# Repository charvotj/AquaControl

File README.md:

# Do not read me :)

It's work in progress and it's still completely uncomplete.

## Pro průběžný progress:
- [Verze odevzdaná jako semestrální](https://github.com/charvotj/AquaControl/tree/main/Semestr%C3%A1lka%20k%20odevzd%C3%A1n%C3%AD)
- [Poslední LaTeX build (text práce)](https://github.com/charvotj/AquaControl/blob/main/latex/CharvotBakalarka2023.pdf)
- [Schéma řídící jednotky (export do pdf)](https://github.com/charvotj/AquaControl/blob/main/latex/obrazky/exportovane/main-board-schematic.pdf)

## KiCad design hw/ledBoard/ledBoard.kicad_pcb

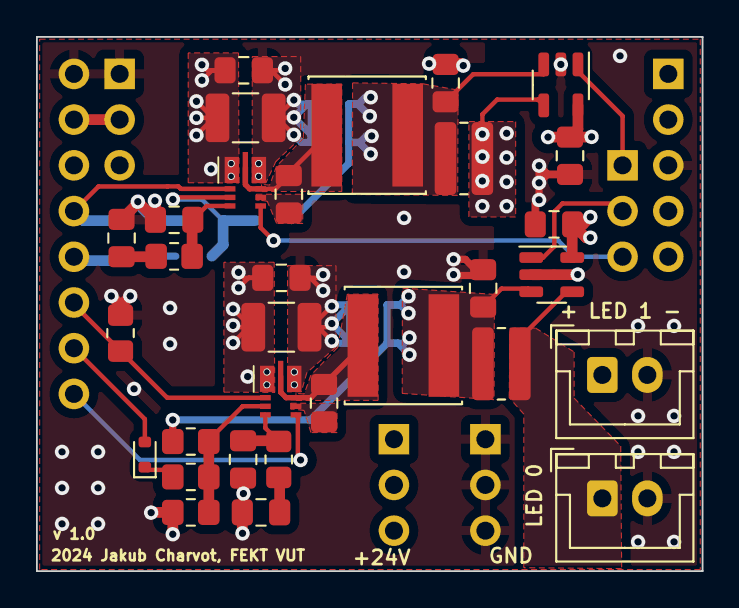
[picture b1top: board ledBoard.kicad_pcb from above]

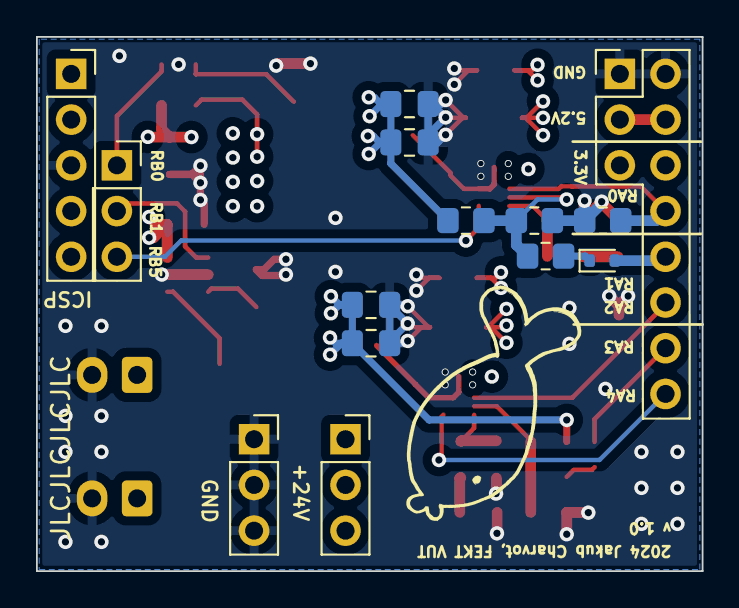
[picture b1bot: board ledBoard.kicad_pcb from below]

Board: 4 copper layers, 37.0 x 29.7 mm, 45 parts (13 on the bottom side), 28 nets.

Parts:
C2, C3: 10uF; C_1210_3225Metric_Pad1.33x2.70mm_HandSolder
C4, C5: 10nF; C_0805_2012Metric_Pad1.18x1.45mm_HandSolder
C6, C14: 6.8nF; C_0805_2012Metric_Pad1.18x1.45mm_HandSolder
C7, C13, C19, C20, C23, C24: 100nF; C_0805_2012Metric_Pad1.18x1.45mm_HandSolder
C8, C9, C10, C15, C16, C17: 22uF; C_0805_2012Metric_Pad1.18x1.45mm_HandSolder
D2, D4: RB501SM; D_SOD-523
J1: Conn_02x11_Socket; LedBoardPinHeader
J2, J3: Conn_01x02; JST_XH_B2B-XH-A_1x02_P2.50mm_Vertical
J5, J6, J9: Conn_01x03_Socket; PinSocket_1x03_P2.54mm_Vertical
J8: Conn_01x05_Socket; PinSocket_1x05_P2.54mm_Vertical
L1, L2: 10uH; L_Changjiang_FNR6045S
R1, R9: 140k; R_0805_2012Metric_Pad1.20x1.40mm_HandSolder
R2, R10: 10k; R_0805_2012Metric_Pad1.20x1.40mm_HandSolder
R3, R7: 47k; R_0805_2012Metric_Pad1.20x1.40mm_HandSolder
R4, R5, R8, R11: 100k; R_0805_2012Metric_Pad1.20x1.40mm_HandSolder
R6, R12: 10m; R_0815_2038Metric_Pad1.20x4.05mm_HandSolder
U1, U2: INA180A4; SOT-23-5
U3, U4: AP63356Q; V-DFN3020-13

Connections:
/5.2V: J1.3, J1.4
/24V: C2.1, C3.1, C4.1, C5.1, J9.1, J9.2, J9.3, U3.1 (VIN), U4.1 (VIN)
/LED_OUT_0: J2.1, R6.1, U1.4 (-)
/LED_OUT_1: J3.1, R12.1, U2.4 (-)
/RA0: J1.8, R8.1, U4.2 (EN)
/RA1: D4.2 (A), J1.10
/RA2: J1.12, R5.1, U3.2 (EN)
/RA3: D2.2 (A), J1.14
/RA4: J1.16, U3.5 (PG)
/RB0: J5.1, U2.1
/RB1: J5.2, U1.1
/RB5: J5.3, U4.5 (PG)
/VDD: C19.1, C20.1, J1.5, J1.6, J8.2, U1.5 (V+), U2.5 (V+)
GND: C2.2, C3.2, C4.2, C5.2, C6.1, C7.1, C8.2, C9.2, C10.2, C13.1, C14.1, C15.2, C16.2, C17.2, C19.2, C20.2, J1.1, J1.2, J2.2, J3.2, J6.1, J6.2, J6.3, J8.3, R2.2, R5.2, R8.2, R10.2, U1.2 (GND), U2.2 (GND), U3.8 (GND), U4.8 (GND)
unnamed: C6.2, R3.2
unnamed: C14.2, R7.2
unnamed: D2.1 (K), R4.2
unnamed: D4.1 (K), R11.2
unnamed: C8.1, C9.1, C10.1, L1.1, R1.1, R6.2, U1.3 (+)
unnamed: C15.1, C16.1, C17.1, L2.1, R9.1, R12.2, U2.3 (+)
unnamed: C24.1, U3.6 (BST)
unnamed: C7.2, R3.1, U3.4 (COMP)
unnamed: R1.2, R2.1, R4.1, U3.3 (FB)
unnamed: C24.2, L1.2, U3.9 (SW)
unnamed: C23.1, U4.6 (BST)
unnamed: C13.2, R7.1, U4.4 (COMP)
unnamed: R9.2, R10.1, R11.1, U4.3 (FB)
unnamed: C23.2, L2.2, U4.9 (SW)

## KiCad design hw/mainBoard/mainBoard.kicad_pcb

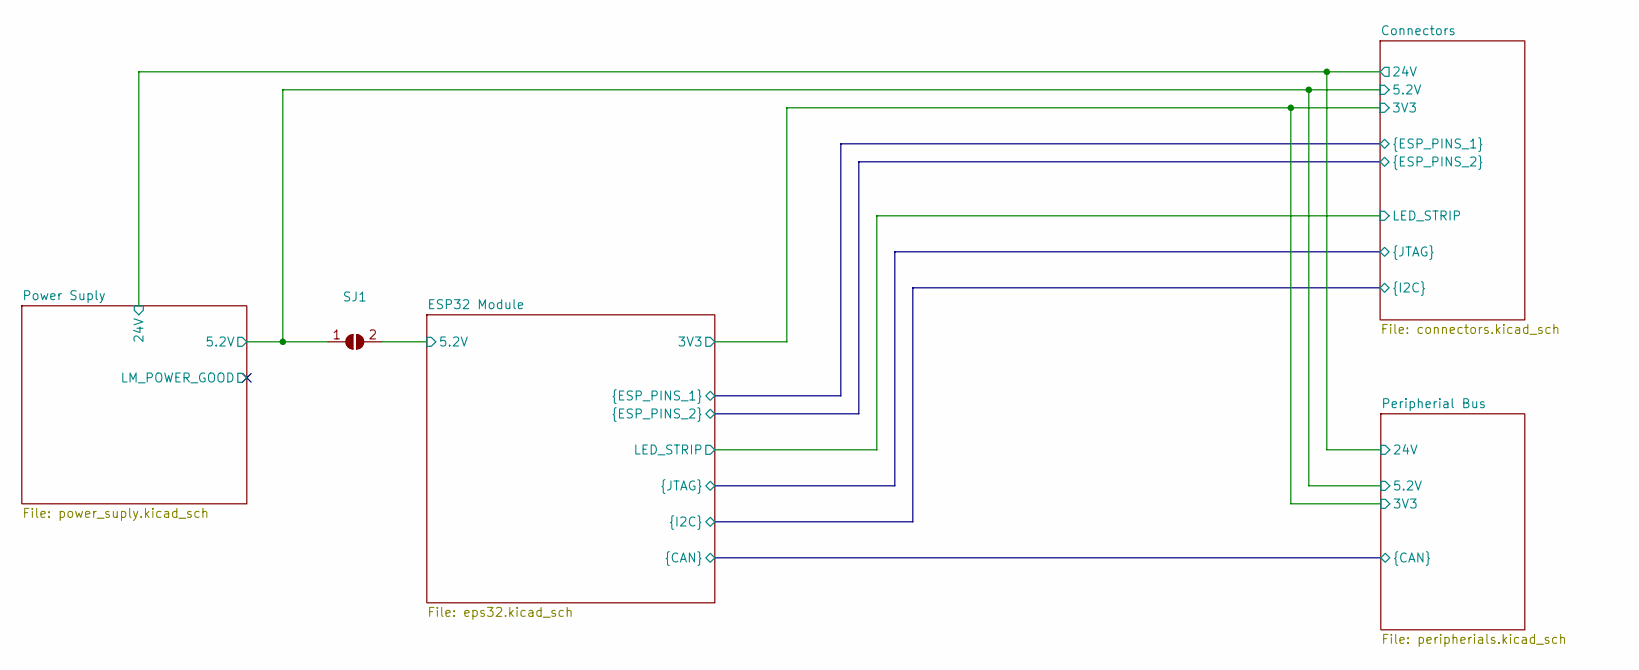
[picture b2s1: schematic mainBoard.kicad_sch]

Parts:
SJ1: SolderJumper_2_Open; SolderJumper-2_P1.3mm_Open_RoundedPad1.0x1.5mm

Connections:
/Connectors/5.2V: SJ1.1 (A), SJ1.2 (B); also elsewhere on the board

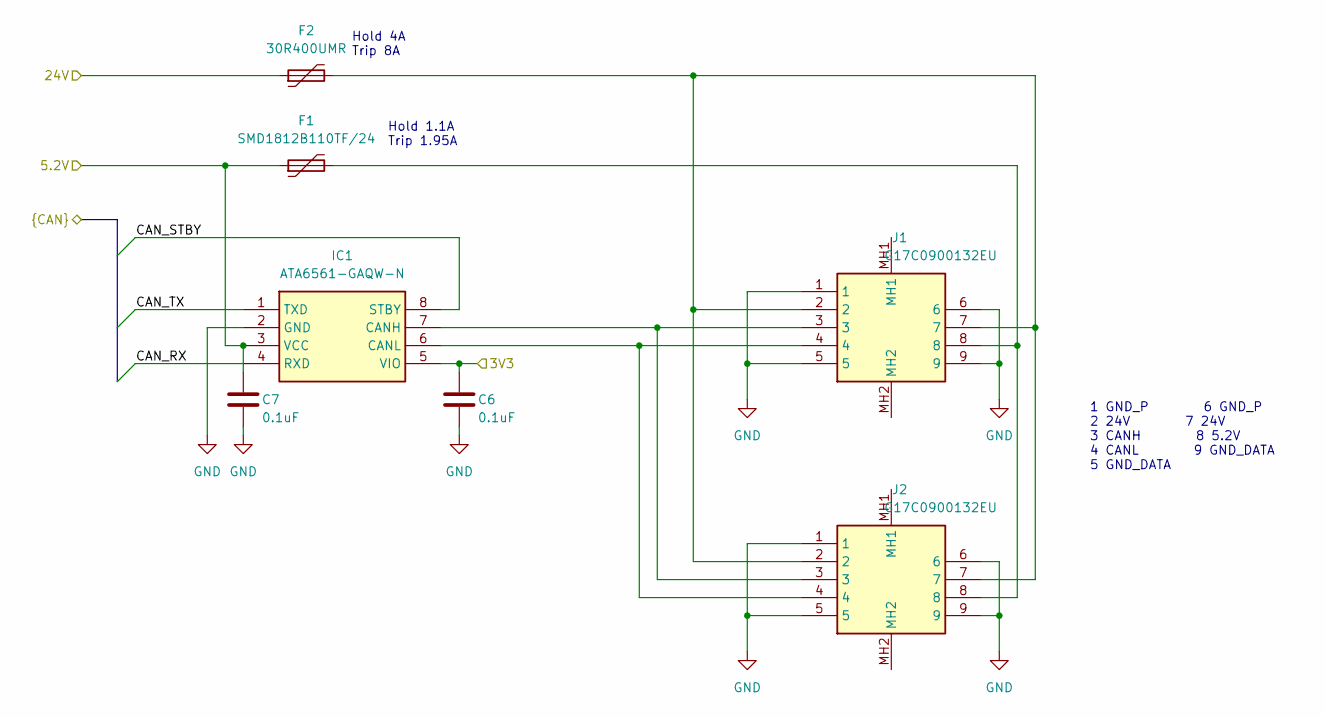
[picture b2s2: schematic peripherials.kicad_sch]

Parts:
C6, C7: 0.1uF; C_1206_3216Metric_Pad1.33x1.80mm_HandSolder
F1: SMD1812B110TF/24; Fuse_1812_4532Metric
F2: 30R400UMR
IC1: ATA6561-GAQW-N; SOIC127P600X175-8N; Mouser Part Number 579-ATA6561-GAQW-N
J1, J2: G17C0900132EU; Mouser Part Number 523-G17C0900132EU

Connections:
/Connectors/5.2V: C7.1, F1.1, IC1.3 (VCC); also elsewhere on the board
/Connectors/24V: F2.1; also elsewhere on the board
/Connectors/CAN_RX: IC1.4 (RXD); also elsewhere on the board
/Connectors/CAN_STBY: IC1.8 (STBY); also elsewhere on the board
/Connectors/CAN_TX: IC1.1 (TXD); also elsewhere on the board
/ESP32 Module/3V3: C6.1, IC1.5 (VIO); also elsewhere on the board
GND: C6.2, C7.2, IC1.2 (GND), J1.1, J1.5, J1.6, J1.9, J2.1, J2.5, J2.6, J2.9; also elsewhere on the board
unnamed: F2.2, J1.2, J1.7, J2.2, J2.7
unnamed: F1.2, J1.8, J2.8
unnamed: IC1.7 (CANH), J1.3, J2.3
unnamed: IC1.6 (CANL), J1.4, J2.4

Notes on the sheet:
Hold 4A Trip 8A
1 GND_P 6 GND_P 2 24V 7 24V 3 CANH 8 5.2V 4 CANL 9 GND_DATA 5 GND_DATA
Hold 1.1A Trip 1.95A

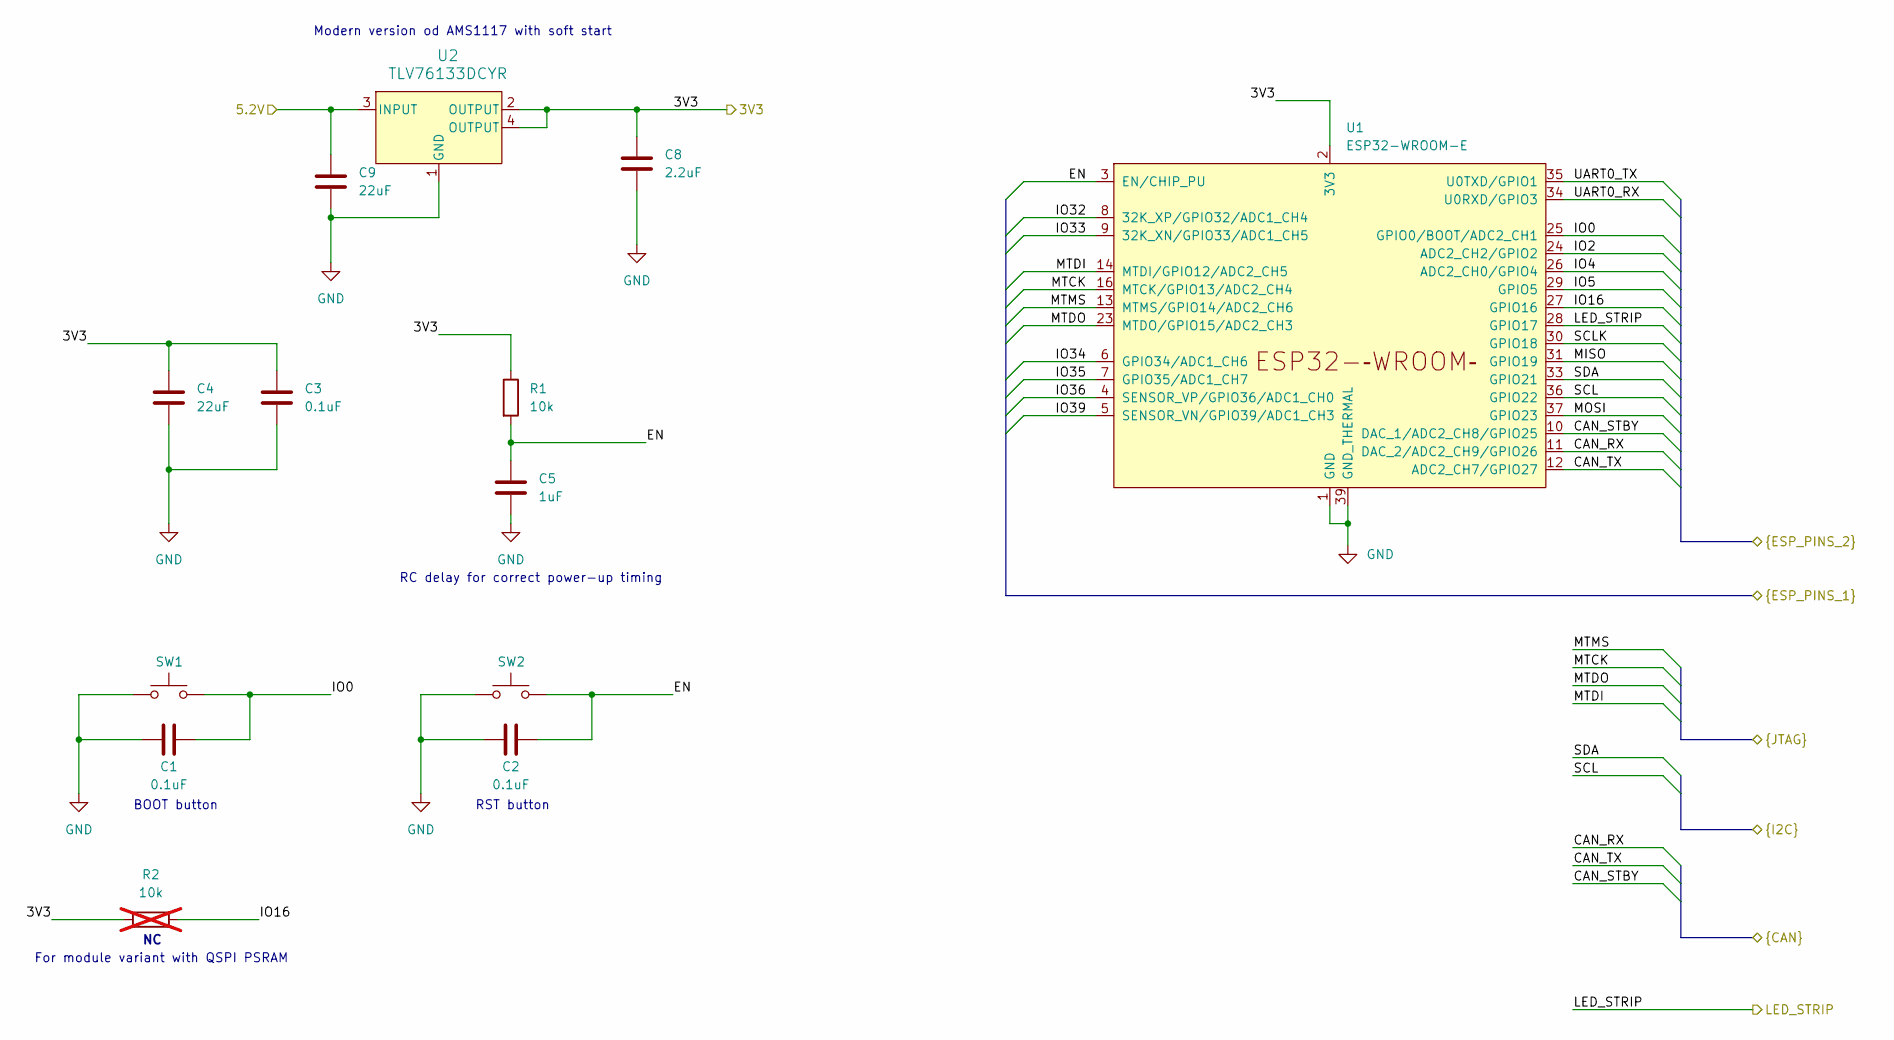
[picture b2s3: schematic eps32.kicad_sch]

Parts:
C1, C2, C3: 0.1uF; C_1206_3216Metric_Pad1.33x1.80mm_HandSolder
C4, C9: 22uF; C_1206_3216Metric_Pad1.33x1.80mm_HandSolder
C5: 1uF; C_1206_3216Metric_Pad1.33x1.80mm_HandSolder
C8: 2.2uF; C_1206_3216Metric_Pad1.33x1.80mm_HandSolder
R1: 10k; R_0805_2012Metric_Pad1.20x1.40mm_HandSolder
R2: 10k; R_0805_2012Metric_Pad1.20x1.40mm_HandSolder; not fitted
SW1, SW2: SW_Push; SW_SPST_B3U-1000P
U1: ESP32-WROOM-E; ESP32-WROOM-32E
U2: TLV76133DCYR; SOT_8DCYR_TEX

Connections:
/Connectors/5.2V: C9.1, U2.3 (INPUT); also elsewhere on the board
/Connectors/CAN_RX: U1.11 (DAC_2/ADC2_CH9/GPIO26); also elsewhere on the board
/Connectors/CAN_STBY: U1.10 (DAC_1/ADC2_CH8/GPIO25); also elsewhere on the board
/Connectors/CAN_TX: U1.12 (ADC2_CH7/GPIO27); also elsewhere on the board
/Connectors/EN: C2.2, C5.1, R1.2, SW2.2, U1.3 (EN/CHIP_PU); also elsewhere on the board
/Connectors/IO0: C1.2, SW1.2, U1.25 (GPIO0/BOOT/ADC2_CH1); also elsewhere on the board
/Connectors/IO2: U1.24 (ADC2_CH2/GPIO2); also elsewhere on the board
/Connectors/IO4: U1.26 (ADC2_CH0/GPIO4); also elsewhere on the board
/Connectors/IO5: U1.29 (GPIO5); also elsewhere on the board
/Connectors/IO16: R2.2, U1.27 (GPIO16); also elsewhere on the board
/Connectors/IO32: U1.8 (32K_XP/GPIO32/ADC1_CH4); also elsewhere on the board
/Connectors/IO33: U1.9 (32K_XN/GPIO33/ADC1_CH5); also elsewhere on the board
/Connectors/IO34: U1.6 (GPIO34/ADC1_CH6); also elsewhere on the board
/Connectors/IO35: U1.7 (GPIO35/ADC1_CH7); also elsewhere on the board
/Connectors/IO36: U1.4 (SENSOR_VP/GPIO36/ADC1_CH0); also elsewhere on the board
/Connectors/IO39: U1.5 (SENSOR_VN/GPIO39/ADC1_CH3); also elsewhere on the board
/Connectors/LED_STRIP: U1.28 (GPIO17); also elsewhere on the board
/Connectors/MISO: U1.31 (GPIO19); also elsewhere on the board
/Connectors/MOSI: U1.37 (GPIO23); also elsewhere on the board
/Connectors/MTCK: U1.16 (MTCK/GPIO13/ADC2_CH4); also elsewhere on the board
/Connectors/MTDI: U1.14 (MTDI/GPIO12/ADC2_CH5); also elsewhere on the board
/Connectors/MTDO: U1.23 (MTDO/GPIO15/ADC2_CH3); also elsewhere on the board
/Connectors/MTMS: U1.13 (MTMS/GPIO14/ADC2_CH6); also elsewhere on the board
/Connectors/SCL: U1.36 (GPIO22); also elsewhere on the board
/Connectors/SCLK: U1.30 (GPIO18); also elsewhere on the board
/Connectors/SDA: U1.33 (GPIO21); also elsewhere on the board
/Connectors/UART0_RX: U1.34 (U0RXD/GPIO3); also elsewhere on the board
/Connectors/UART0_TX: U1.35 (U0TXD/GPIO1); also elsewhere on the board
/ESP32 Module/3V3: C3.1, C4.1, C8.1, R1.1, R2.1, U1.2 (3V3), U2.2 (OUTPUT), U2.4 (OUTPUT); also elsewhere on the board
GND: C1.1, C2.1, C3.2, C4.2, C5.2, C8.2, C9.2, SW1.1, SW2.1, U1.1 (GND), U1.15 (GND), U1.38 (GND), U1.39 (GND_THERMAL), U2.1 (GND); also elsewhere on the board

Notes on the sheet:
RST button
BOOT button
Modern version od AMS1117 with soft start
For module variant with QSPI PSRAM
RC delay for correct power-up timing

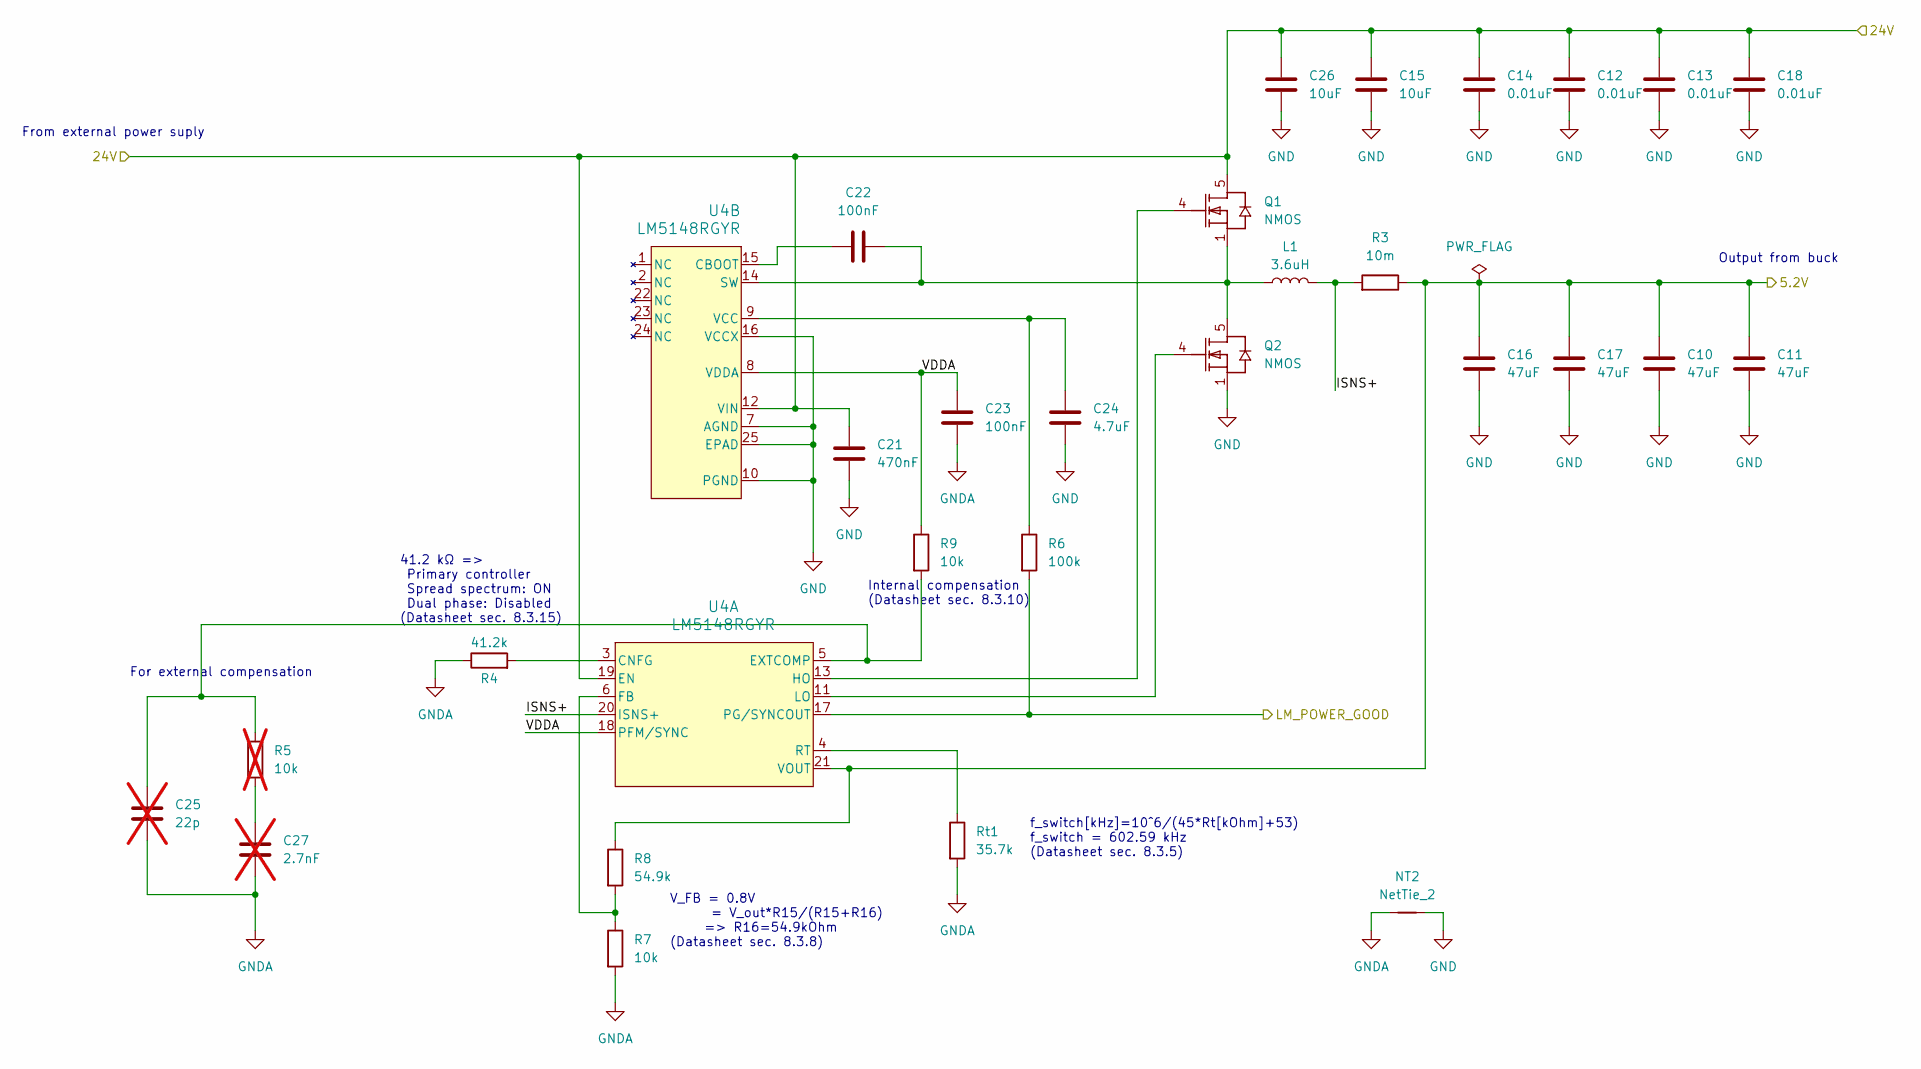
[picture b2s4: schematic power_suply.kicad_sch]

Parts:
C10, C11, C16, C17: 47uF; C_1210_3225Metric_Pad1.33x2.70mm_HandSolder
C12, C13, C14, C18: 0.01uF; C_0805_2012Metric_Pad1.18x1.45mm_HandSolder
C15, C26: 10uF; C_1210_3225Metric_Pad1.33x2.70mm_HandSolder
C21: 470nF; C_0805_2012Metric_Pad1.18x1.45mm_HandSolder
C22, C23: 100nF; C_0805_2012Metric_Pad1.18x1.45mm_HandSolder
C24: 4.7uF; C_0805_2012Metric_Pad1.18x1.45mm_HandSolder
C25: 22p; C_0805_2012Metric_Pad1.18x1.45mm_HandSolder; not fitted
C27: 2.7nF; C_0805_2012Metric_Pad1.18x1.45mm_HandSolder; not fitted
L1: 3.6uH; L_Bourns-SRN8040_8x8.15mm
NT2: NetTie_2; NetTie-2_SMD_Pad0.5mm
Q1, Q2: NMOS; DQJ0008A
R3: 10m; R_0815_2038Metric_Pad1.20x4.05mm_HandSolder
R4: 41.2k; R_0805_2012Metric_Pad1.20x1.40mm_HandSolder
R5: 10k; R_0805_2012Metric_Pad1.20x1.40mm_HandSolder; not fitted
R6: 100k; R_0805_2012Metric_Pad1.20x1.40mm_HandSolder
R7, R9: 10k; R_0805_2012Metric_Pad1.20x1.40mm_HandSolder
R8: 54.9k; R_0805_2012Metric_Pad1.20x1.40mm_HandSolder
Rt1: 35.7k; R_0805_2012Metric_Pad1.20x1.40mm_HandSolder
U4: LM5148RGYR; VQFN24_RGY_TEX

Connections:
/Connectors/5.2V: C10.1, C11.1, C16.1, C17.1, R3.1, R8.1, U4.21 (VOUT); also elsewhere on the board
/Connectors/24V: C12.1, C13.1, C14.1, C15.1, C18.1, C21.1, C26.1, Q1.5, Q1.6 (D), Q1.7 (D), Q1.8 (D), Q1.9, U4.12 (VIN), U4.19 (EN); also elsewhere on the board
/Power Suply/ISNS+: L1.1, R3.2, U4.20 (ISNS+)
/Power Suply/LM_POWER_GOOD: R6.2, U4.17 (PG/SYNCOUT)
/Power Suply/VDDA: C23.1, R9.1, U4.8 (VDDA), U4.18 (PFM/SYNC)
GND: C10.2, C11.2, C12.2, C13.2, C14.2, C15.2, C16.2, C17.2, C18.2, C21.2, C24.2, C26.2, NT2.2, Q2.1, Q2.2 (S), Q2.3 (S), U4.1 (NC), U4.7 (AGND), U4.10 (PGND), U4.16 (VCCX), U4.22 (NC), U4.23 (NC), U4.24 (NC), U4.25 (EPAD); also elsewhere on the board
GNDA: C23.2, C25.2, C27.2, NT2.1, R4.1, R7.2, Rt1.2; also elsewhere on the board
unnamed: C27.1, R5.2
unnamed: C25.1, R5.1, R9.2, U4.5 (EXTCOMP)
unnamed: R7.1, R8.2, U4.6 (FB)
unnamed: Q1.4, U4.13 (HO)
unnamed: Q2.4, U4.11 (LO)
unnamed: Rt1.1, U4.4 (RT)
unnamed: C22.1, U4.15 (CBOOT)
unnamed: C22.2, L1.2, Q1.1, Q1.2 (S), Q1.3 (S), Q2.5, Q2.6 (D), Q2.7 (D), Q2.8 (D), Q2.9, U4.14 (SW)
unnamed: C24.1, R6.1, U4.9 (VCC)

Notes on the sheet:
From external power suply
For external compensation
f_switch[kHz]=10^6/(45*Rt[kOhm]+53) f_switch = 602.59 kHz (Datasheet sec. 8.3.5)
Output from buck
41.2 kΩ => Primary controller Spread spectrum: ON Dual phase: Disabled (Datasheet sec. 8.3.15)
Internal compensation (Datasheet sec. 8.3.10)
V_FB = 0.8V = V_out*R15/(R15+R16) => R16=54.9kOhm (Datasheet sec. 8.3.8)

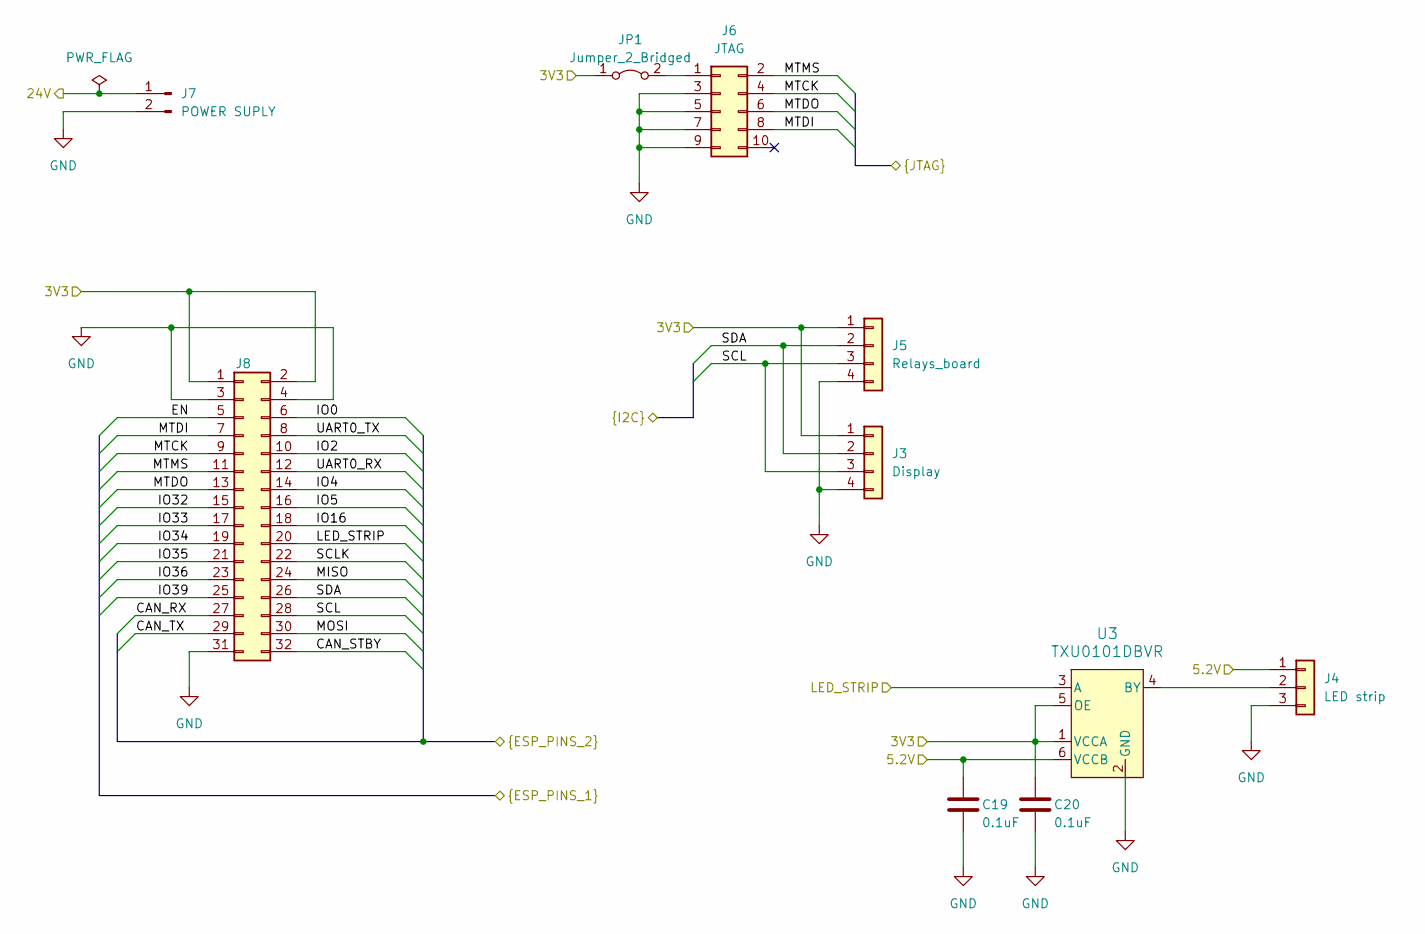
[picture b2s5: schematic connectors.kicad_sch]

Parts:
C19, C20: 0.1uF; C_1206_3216Metric_Pad1.33x1.80mm_HandSolder
J3: Display; JST_XH_B4B-XH-AM_1x04_P2.50mm_Vertical
J4: LED strip; JST_EH_B3B-EH-A_1x03_P2.50mm_Vertical
J5: Relays_board; JST_XH_B4B-XH-AM_1x04_P2.50mm_Vertical
J6: JTAG; PinHeader_2x05_P1.27mm_Vertical
J7: POWER SUPLY; TerminalBlock_Altech_AK300-2_P5.00mm
J8: Conn_02x16_Odd_Even; PinHeader_2x16_P2.54mm_Vertical
JP1: Jumper_2_Bridged; TestPoint_2Pads_Pitch2.54mm_Drill0.8mm
U3: TXU0101DBVR; SOT-23-6-DBV_TEX

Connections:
/Connectors/5.2V: C19.1, J4.1, U3.6 (VCCB); also elsewhere on the board
/Connectors/24V: J7.1; also elsewhere on the board
/Connectors/CAN_RX: J8.27; also elsewhere on the board
/Connectors/CAN_STBY: J8.32; also elsewhere on the board
/Connectors/CAN_TX: J8.29; also elsewhere on the board
/Connectors/EN: J8.5; also elsewhere on the board
/Connectors/IO0: J8.6; also elsewhere on the board
/Connectors/IO2: J8.10; also elsewhere on the board
/Connectors/IO4: J8.14; also elsewhere on the board
/Connectors/IO5: J8.16; also elsewhere on the board
/Connectors/IO16: J8.18; also elsewhere on the board
/Connectors/IO32: J8.15; also elsewhere on the board
/Connectors/IO33: J8.17; also elsewhere on the board
/Connectors/IO34: J8.19; also elsewhere on the board
/Connectors/IO35: J8.21; also elsewhere on the board
/Connectors/IO36: J8.23; also elsewhere on the board
/Connectors/IO39: J8.25; also elsewhere on the board
/Connectors/LED_STRIP: J8.20, U3.3 (A); also elsewhere on the board
/Connectors/MISO: J8.24; also elsewhere on the board
/Connectors/MOSI: J8.30; also elsewhere on the board
/Connectors/MTCK: J6.4, J8.9; also elsewhere on the board
/Connectors/MTDI: J6.8, J8.7; also elsewhere on the board
/Connectors/MTDO: J6.6, J8.13; also elsewhere on the board
/Connectors/MTMS: J6.2, J8.11; also elsewhere on the board
/Connectors/SCL: J3.3, J5.3, J8.28; also elsewhere on the board
/Connectors/SCLK: J8.22; also elsewhere on the board
/Connectors/SDA: J3.2, J5.2, J8.26; also elsewhere on the board
/Connectors/UART0_RX: J8.12; also elsewhere on the board
/Connectors/UART0_TX: J8.8; also elsewhere on the board
/ESP32 Module/3V3: C20.1, J3.1, J5.1, J8.1, J8.2, JP1.1 (A), U3.1 (VCCA), U3.5 (OE); also elsewhere on the board
GND: C19.2, C20.2, J3.4, J4.3, J5.4, J6.3, J6.5, J6.7, J6.9, J7.2, J8.3, J8.4, J8.31, U3.2 (GND); also elsewhere on the board
unnamed: J4.2, U3.4 (BY)
unnamed: J6.1, JP1.2 (B)

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
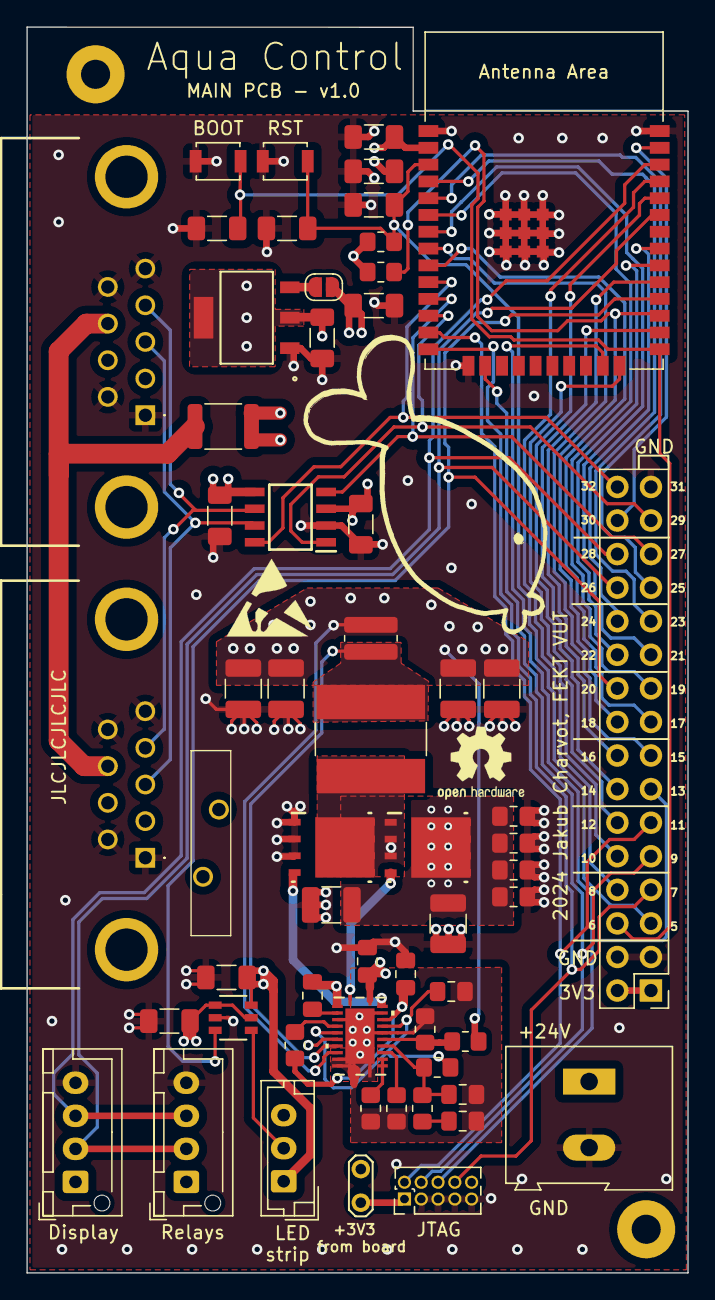
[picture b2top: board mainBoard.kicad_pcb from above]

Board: 4 copper layers, 50.0 x 94.2 mm, 62 parts (0 on the bottom side), 51 nets.

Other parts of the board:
BOOT: SW_Push; SW_SPST_B3U-1000P
NT1: NetTie_2; NetTie-2_SMD_Pad0.5mm
RST: SW_Push; SW_SPST_B3U-1000P
RYBA: LOGO

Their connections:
/Connectors/EN: RST.2; also elsewhere on the board
/Connectors/IO0: BOOT.2; also elsewhere on the board
GND: BOOT.1, NT1.2, RST.1; also elsewhere on the board
GNDA: NT1.1; also elsewhere on the board

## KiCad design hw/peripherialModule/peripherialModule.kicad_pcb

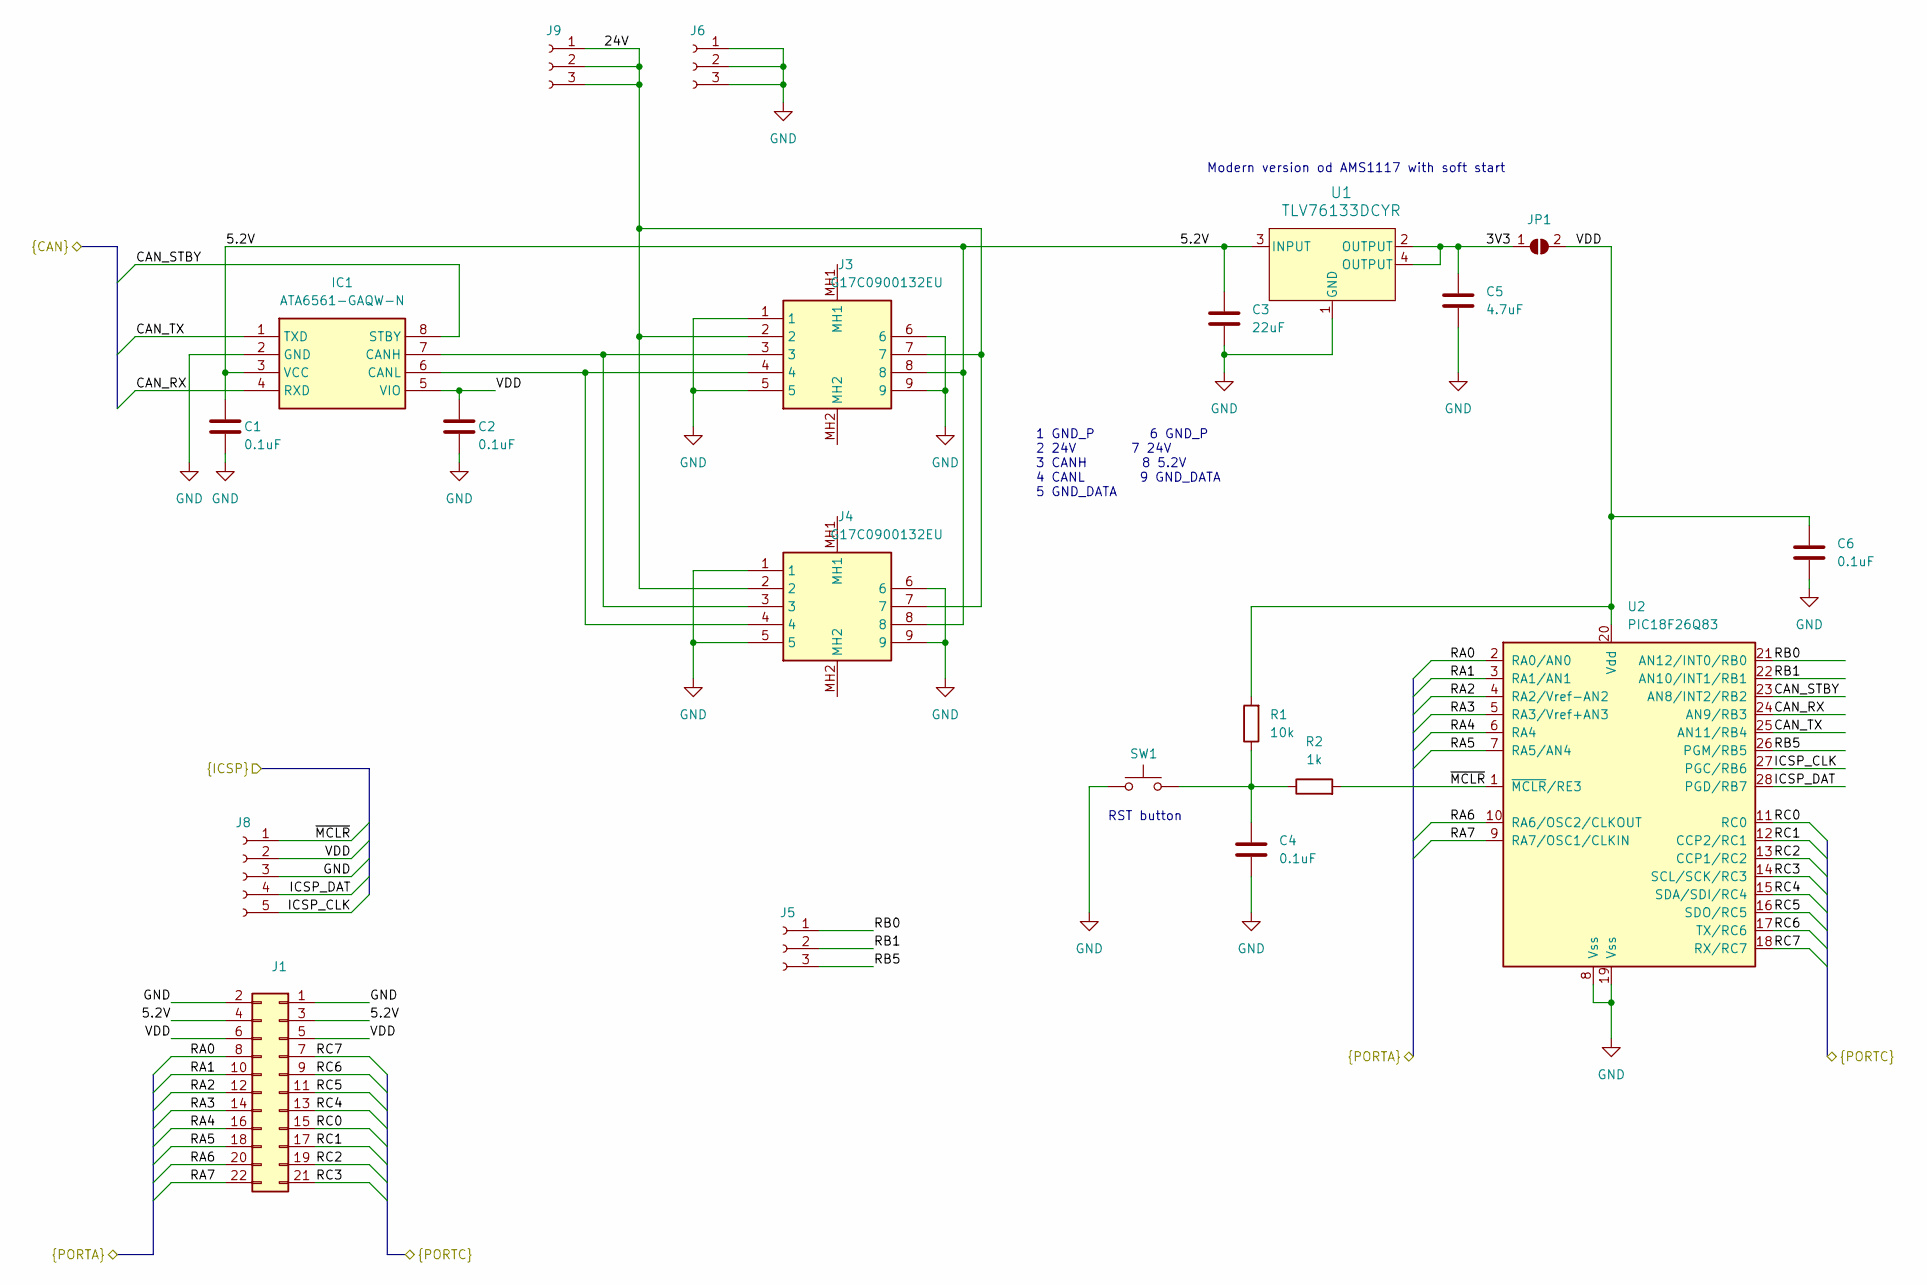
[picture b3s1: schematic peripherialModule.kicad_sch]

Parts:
C1, C2: 0.1uF; C_1206_3216Metric_Pad1.33x1.80mm_HandSolder
C3: 22uF; C_1206_3216Metric_Pad1.33x1.80mm_HandSolder
C4, C6: 0.1uF; C_1206_3216Metric_Pad1.33x1.80mm_HandSolder; Mouser no. 80-C1206C104K5R7210
C5: 4.7uF; C_0805_2012Metric_Pad1.18x1.45mm_HandSolder
IC1: ATA6561-GAQW-N; SOIC127P600X175-8N; Mouser Part Number 579-ATA6561-GAQW-N
J1: Conn_02x11_Socket; PinSocket_2x11_P2.54mm_Vertical
J3, J4: G17C0900132EU; Mouser Part Number 523-G17C0900132EU
J5, J6, J9: Conn_01x03_Socket; PinSocket_1x03_P2.54mm_Vertical
J8: Conn_01x05_Socket; PinSocket_1x05_P2.54mm_Vertical
JP1: SolderJumper_2_Open; SolderJumper-2_P1.3mm_Open_RoundedPad1.0x1.5mm
R1: 10k; R_0805_2012Metric_Pad1.20x1.40mm_HandSolder; Mouser no. 791-RMC20K103FTP
R2: 1k; R_0805_2012Metric_Pad1.20x1.40mm_HandSolder
SW1: SW_Push; SW_SPST_B3U-1000P
U1: TLV76133DCYR; SOT_8DCYR_TEX
U2: PIC18F26Q83; SSOP-28_5.3x10.2mm_P0.65mm

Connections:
/3V3: C5.1, JP1.1 (A), U1.2 (OUTPUT), U1.4 (OUTPUT)
/5.2V: C1.1, C3.1, IC1.3 (VCC), J1.3, J1.4, J3.8, J4.8, U1.3 (INPUT)
/24V: J3.2, J3.7, J4.2, J4.7, J9.1, J9.2, J9.3
/CAN_RX: IC1.4 (RXD), U2.24 (AN9/RB3)
/CAN_STBY: IC1.8 (STBY), U2.23 (AN8/INT2/RB2)
/CAN_TX: IC1.1 (TXD), U2.25 (AN11/RB4)
/ICSP_CLK: J8.5, U2.27 (PGC/RB6)
/ICSP_DAT: J8.4, U2.28 (PGD/RB7)
/RA0: J1.8, U2.2 (RA0/AN0)
/RA1: J1.10, U2.3 (RA1/AN1)
/RA2: J1.12, U2.4 (RA2/Vref-AN2)
/RA3: J1.14, U2.5 (RA3/Vref+AN3)
/RA4: J1.16, U2.6 (RA4)
/RA5: J1.18, U2.7 (RA5/AN4)
/RA6: J1.20, U2.10 (RA6/OSC2/CLKOUT)
/RA7: J1.22, U2.9 (RA7/OSC1/CLKIN)
/RB0: J5.1, U2.21 (AN12/INT0/RB0)
/RB1: J5.2, U2.22 (AN10/INT1/RB1)
/RB5: J5.3, U2.26 (PGM/RB5)
/RC0: J1.15, U2.11 (RC0)
/RC1: J1.17, U2.12 (CCP2/RC1)
/RC2: J1.19, U2.13 (CCP1/RC2)
/RC3: J1.21, U2.14 (SCL/SCK/RC3)
/RC4: J1.13, U2.15 (SDA/SDI/RC4)
/RC5: J1.11, U2.16 (SDO/RC5)
/RC6: J1.9, U2.17 (TX/RC6)
/RC7: J1.7, U2.18 (RX/RC7)
/VDD: C2.1, C6.1, IC1.5 (VIO), J1.5, J1.6, J8.2, JP1.2 (B), R1.2, U2.20 (Vdd)
/~MCLR: J8.1, R2.2, U2.1 (~MCLR/RE3)
GND: C1.2, C2.2, C3.2, C4.2, C5.2, C6.2, IC1.2 (GND), J1.1, J1.2, J3.1, J3.5, J3.6, J3.9, J4.1, J4.5, J4.6, J4.9, J6.1, J6.2, J6.3, J8.3, SW1.1, U1.1 (GND), U2.8 (Vss), U2.19 (Vss)
unnamed: C4.1, R1.1, R2.1, SW1.2
unnamed: IC1.7 (CANH), J3.3, J4.3
unnamed: IC1.6 (CANL), J3.4, J4.4

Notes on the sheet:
1 GND_P 6 GND_P 2 24V 7 24V 3 CANH 8 5.2V 4 CANL 9 GND_DATA 5 GND_DATA
RST button
Modern version od AMS1117 with soft start

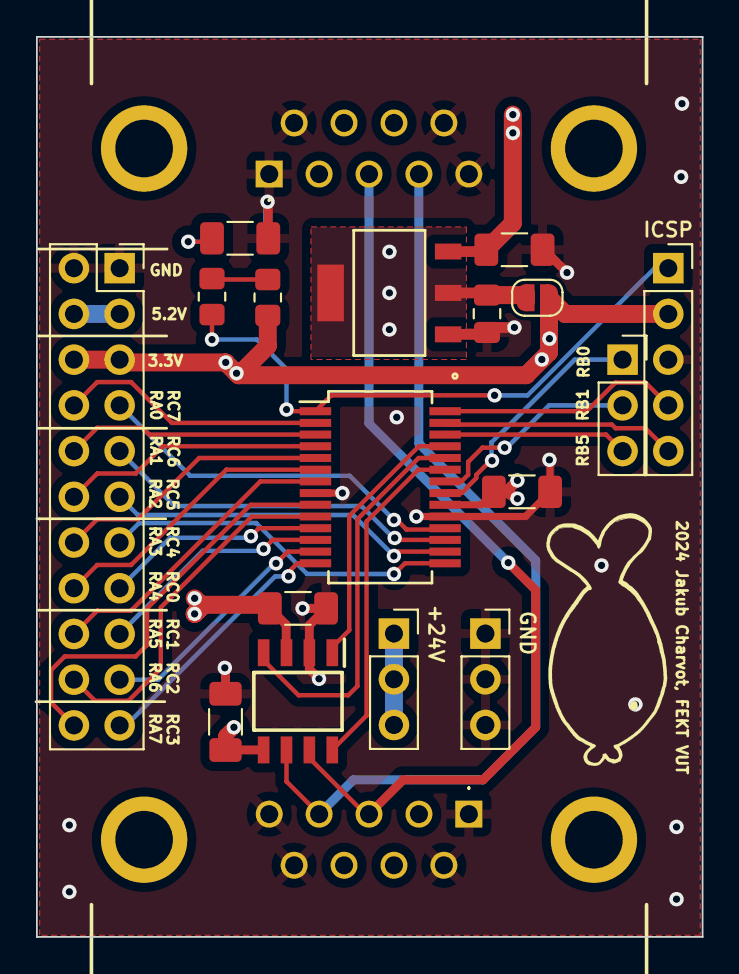
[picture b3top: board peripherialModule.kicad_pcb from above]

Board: 4 copper layers, 37.0 x 50.0 mm, 20 parts (1 on the bottom side), 33 nets.

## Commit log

2023-06-20 uvodni poznamky
2023-06-20 better names
2023-09-27 trh + plan prace
2023-10-09 sablona prace + zmena adresaru
2023-11-03 sablona, struktura, uvod
2023-11-09 gitignore
2023-11-12 hw - schema work in progress
2023-11-13 hw - schema temp
2023-11-17 hw - kicad neco
2023-11-19 latex - historie + rozdeleni
2023-12-03 hw + blok schema
2023-12-05 nejaky hw + teorie + desky
2023-12-07 moc věcí
2023-12-07 schema temp
2023-12-08 komit
2023-12-08 hw - changed uart2 pins, latex- ridici jednotka
2023-12-08 schematka
2023-12-11 text - napajeci obvod, ochrany, 230v + pomocne schema v kicadu
2023-12-11 rid mi
2023-12-11 hw - rezistory
2023-12-12 text - vetsina pruzkumu trhu
2023-12-12 seneye
2023-12-13 text - obecna periferie
2023-12-13 pH a CO2
2023-12-13 prvni cteni
2023-12-13 citace
2023-12-13 zkratky
2023-12-13 dikec
2023-12-13 priloha a nektera todo
2023-12-14 zaver
2023-12-14 abtract + keywords
2023-12-14 vlna
2023-12-14 clean
2023-12-14 Captions
2023-12-14 Seznam vypisu pryc
2023-12-14 Na krásu
2023-12-14 semestralka do systemu
2023-12-14 typo
2023-12-17 v teto verzi odevzdano
2023-12-17 obsidian
2023-12-17 struktura a cleanup
2023-12-17 not read me
2023-12-17 minor changes is the best commit message, change my mind
2024-01-07 prezentace - zacatek
2024-01-08 prezentace makame
2024-01-08 prezentace hotova
2024-01-08 prezentace - na necisto
2024-01-10 Úprava prezentace
2024-02-06 drawing layout
2024-02-06 more steps to the finale
2024-02-10 lot of hw
2024-02-10 buck vedle
2024-02-11 hotovo bez silkscreenu
2024-02-11 finale bez rybicky
2024-02-11 gerbers
2024-02-11 gerbere s rybou
2024-02-14 gerber zip
2024-02-19 moc toho
2024-03-06 boards are changing
2024-03-20 hw - ledBoard
2024-03-20 hw - ledboard, compensation
2024-03-31 hw - led board redesign
2024-04-09 text -- notes obsah prace
2024-04-10 sw - init main fw
2024-05-02 hw - bom
2024-05-02 tex - cleanup a nejake psani
2024-05-02 notes and thouths
2024-05-02 sw - tasks, led strip
2024-05-02 tex - systemovy navrh revised
2024-05-08 sw - peripherial init and mainBoard status leds
2024-05-11 sw - temp sensor master + slave, general things
2024-05-12 FW 0.1 - temp sensor
2024-05-14 sw - water level rozpracovano
2024-05-14 text - dps hlavni jednotky, not final
2024-05-14 text - modul periferie
2024-05-14 text - periferie, obrazky hw - schemata
2024-05-15 nove titulky
2024-05-15 schemata a 3d modely pro text
2024-05-15 text-modul periferie + led board
2024-05-16 text - revize napsaneho, schema lm
2024-05-16 text - temp cidlo
2024-05-16 text: ke prubezne kontrole
2024-05-16 drobna revize
2024-05-19 text - rozpracovani revize od Pavla
2024-05-19 sw - mainBoard wifi and i2c relays
2024-05-22 sw - bugfix can mutex release
2024-05-22 sw - debug
2024-05-22 sw - wifi send api data
2024-05-24 sw - perif, WL, boye
2024-05-24 sw - cJSON lib
2024-05-24 sw - wifi and status better handling
2024-05-24 sw - perif, pins corrected
2024-05-24 cJSON again
2024-05-24 sw - get conf version from web
2024-05-24 text - 230v, wl sensor
2024-05-25 text - software
2024-05-25 text - oprava gramatiky
2024-05-25 text - zkratky + jedno typo
2024-05-25 sw - load config from web, save and load nvm
2024-05-26 prilohy
2024-05-26 text - todo solved and pavlova revize done (almost
2024-05-27 correct payload info
2024-05-27 sw - control routine forst half + many bugfixes
2024-05-27 get and store cfg from web
2024-05-27 text - M <3
2024-05-28 oprava schematicu
2024-05-28 text - lm5148 vypocty a layout
2024-05-28 foto a text o softwaru
2024-05-29 testovani a ph
2024-05-29 uvod, zaver
2024-05-29 podek
2024-05-30 finale vseho
2024-06-06 sw - some rework
2024-06-07 prezentace obhajoba
2024-06-09 memory leak + led improve
2024-06-09 also this
2024-06-09 obhajoba nove foto + oponent
